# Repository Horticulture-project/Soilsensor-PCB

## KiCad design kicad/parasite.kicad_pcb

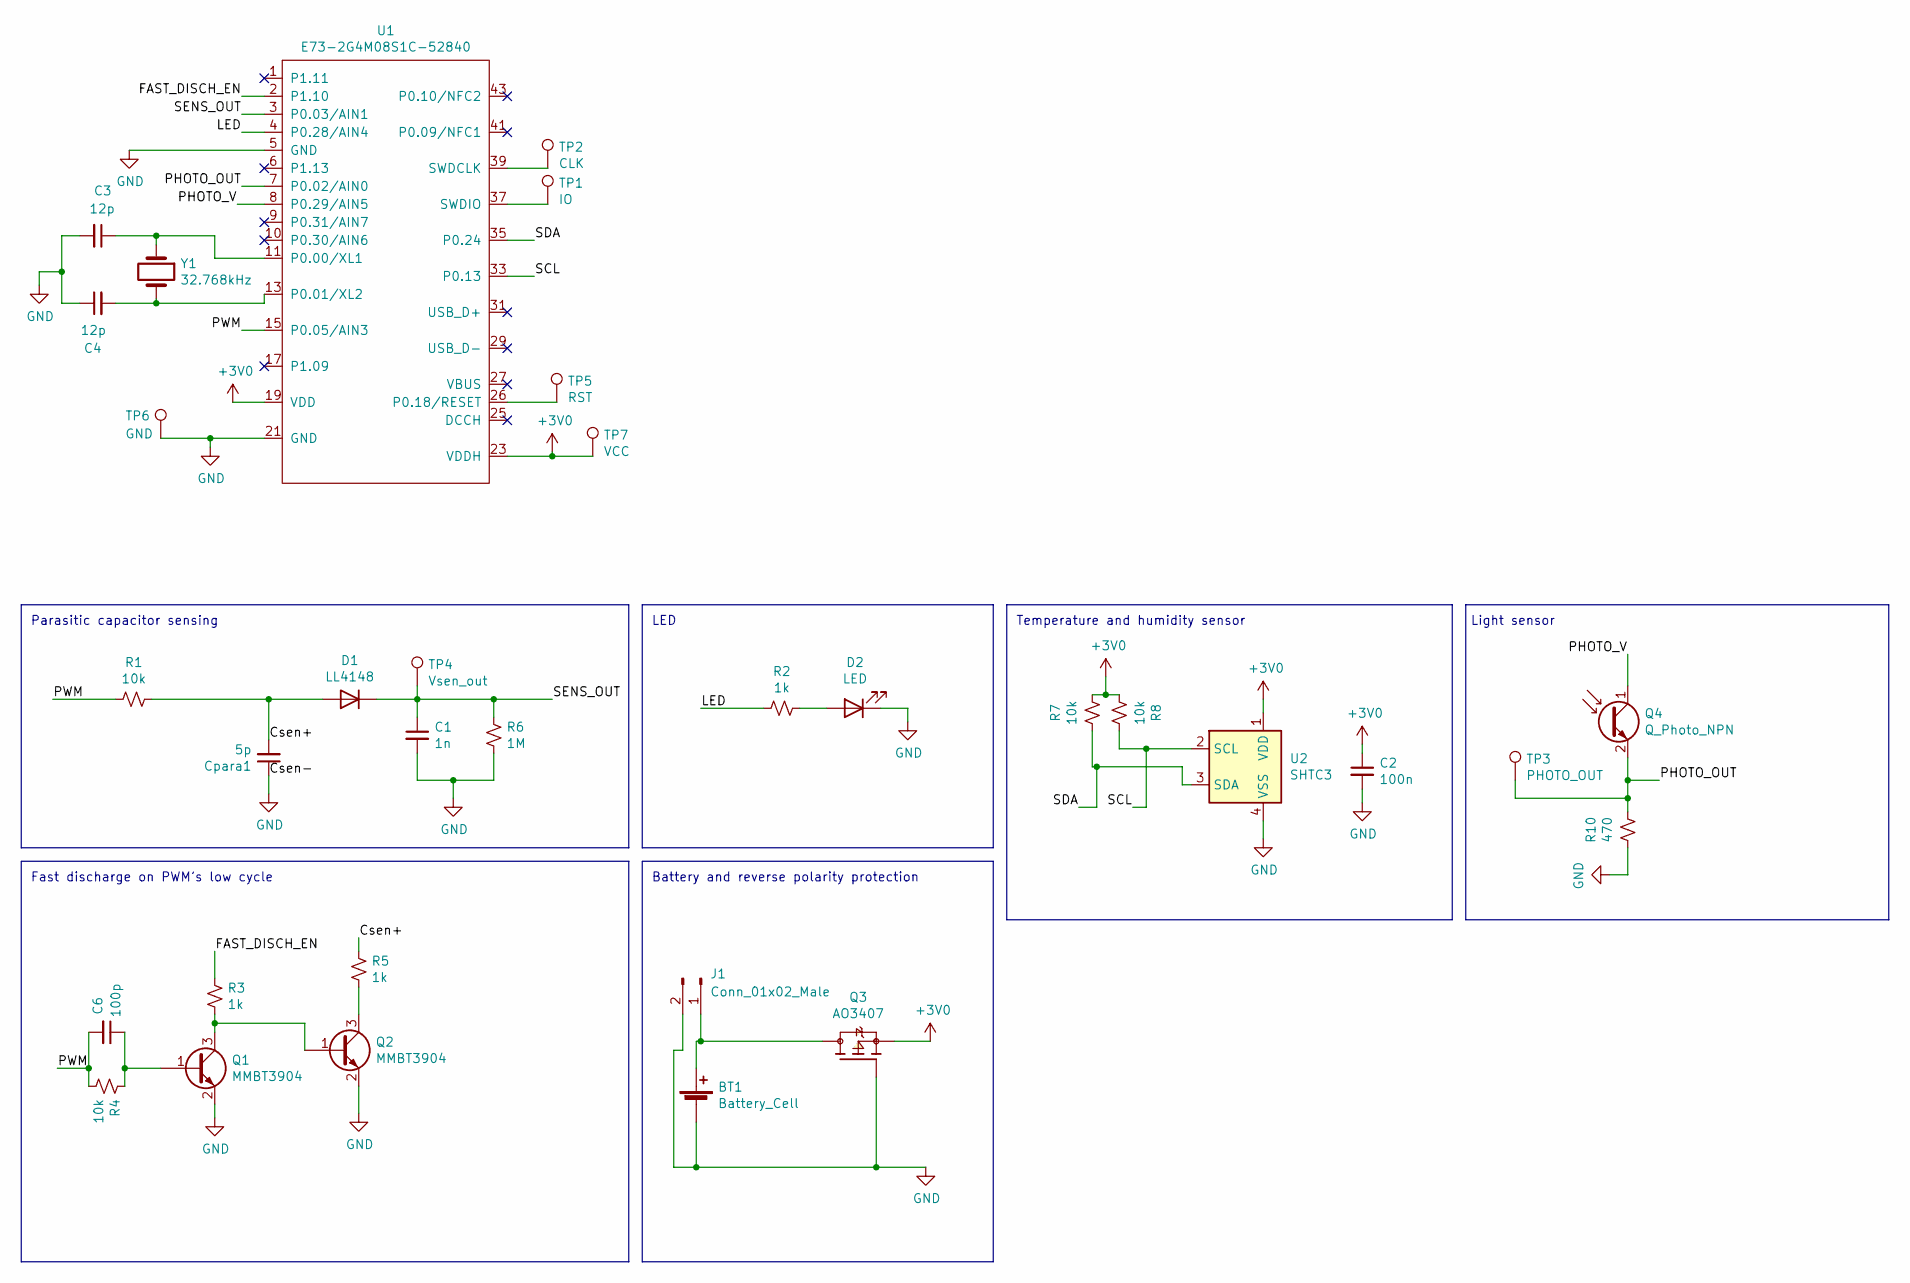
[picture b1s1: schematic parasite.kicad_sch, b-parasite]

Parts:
BT1: Battery_Cell; BatteryHolder_Keystone_3002_1x2032
C1: 1n; C_0402_1005Metric; LCSC C1523
C2: 100n; C_0402_1005Metric; LCSC C1525
C3, C4: 12p; C_0402_1005Metric; LCSC C1547
C6: 100p; C_0402_1005Metric; LCSC C1546
Cpara1: 5p; C_0805_2012Metric
D1: LL4148; D_MiniMELF; LCSC C9808
D2: LED; LED_0603_1608Metric; LCSC C2286
J1: Conn_01x02_Male; Molex_PicoBlade_53261-0271_1x02-1MP_P1.25mm_Horizontal
Q1, Q2: MMBT3904; SOT-23; LCSC C20526
Q3: AO3407; SOT-23; LCSC C181093
Q4: Q_Photo_NPN; TR8; LCSC C146233
R1, R4, R7, R8: 10k; R_0402_1005Metric; LCSC C25744
R2, R3, R5: 1k; R_0402_1005Metric; LCSC C11702
R6: 1M; R_0402_1005Metric; LCSC C26083
R10: 470; R_0402_1005Metric; LCSC C25117
TP1: IO; TestPoint_Pad_D1.0mm
TP2: CLK; TestPoint_Pad_D1.0mm
TP3: PHOTO_OUT; TestPoint_Pad_D1.0mm
TP4: Vsen_out; TestPoint_Pad_D1.0mm
TP5: RST; TestPoint_Pad_D1.0mm
TP6: GND; TestPoint_Pad_D1.0mm
TP7: VCC; TestPoint_Pad_D1.0mm
U1: E73-2G4M08S1C-52840; LCSC C356849
U2: SHTC3; Sensirion_DFN-4-1EP_2x2mm_P1mm_EP0.7x1.6mm; LCSC C194656
Y1: 32.768kHz; Crystal_SMD_3215-2Pin_3.2x1.5mm; LCSC C32346

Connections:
+3V0: C2.1, Q3.2, R7.2, R8.1, TP7.1, U1.19 (VDD), U1.23 (VDDH), U2.1 (VDD)
/Csen+: Cpara1.2, D1.2 (A), R1.2, R5.1
/FAST_DISCH_EN: R3.1, U1.2 (P1.10)
/LED: R2.1, U1.4 (P0.28/AIN4)
/PHOTO_OUT: Q4.2 (E), R10.2, TP3.1, U1.7 (P0.02/AIN0)
/PHOTO_V: Q4.1 (C), U1.8 (P0.29/AIN5)
/PWM: C6.2, R1.1, R4.2, U1.15 (P0.05/AIN3)
/SCL: R8.2, U1.33 (P0.13), U2.2 (SCL)
/SDA: R7.1, U1.35 (P0.24), U2.3 (SDA)
/SENS_OUT: C1.1, D1.1 (K), R6.1, TP4.1, U1.3 (P0.03/AIN1)
GND: BT1.2 (-), C1.2, C2.2, C3.2, C4.1, Cpara1.1, D2.1 (K), J1.2, J1.MP, Q1.2 (E), Q2.2 (E), Q3.1, R6.2, R10.1, TP6.1, U1.5 (GND), U1.21 (GND), U2.4 (VSS)
unnamed: BT1.1 (+), J1.1, Q3.3
unnamed: C3.1, U1.11 (P0.00/XL1), Y1.1
unnamed: C4.2, U1.13 (P0.01/XL2), Y1.2
unnamed: C6.1, Q1.1 (B), R4.1
unnamed: D2.2 (A), R2.2
unnamed: Q1.3 (C), Q2.1 (B), R3.2
unnamed: Q2.3 (C), R5.2
unnamed: TP1.1, U1.37 (SWDIO)
unnamed: TP2.1, U1.39 (SWDCLK)
unnamed: TP5.1, U1.26 (P0.18/RESET)

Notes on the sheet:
Light sensor
Battery and reverse polarity protection
Temperature and humidity sensor
Parasitic capacitor sensing
LED
Fast discharge on PWM’s low cycle

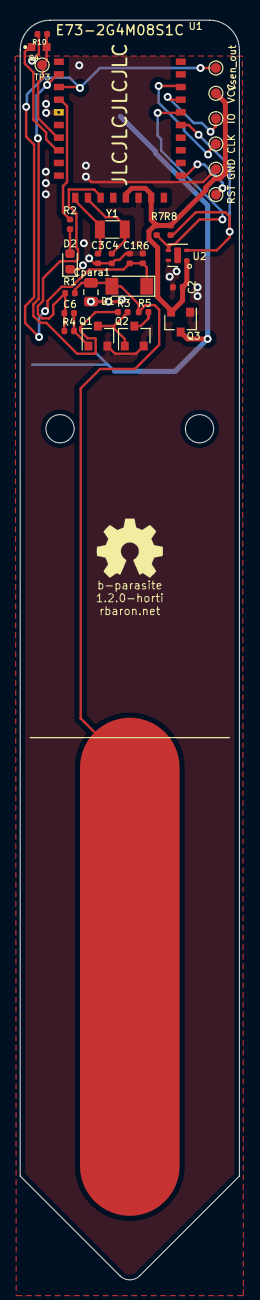
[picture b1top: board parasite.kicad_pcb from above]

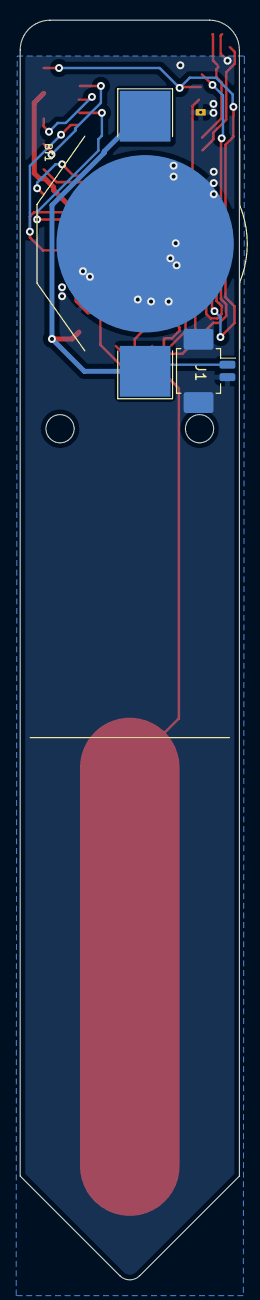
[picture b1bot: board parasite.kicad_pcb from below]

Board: 2 copper layers, 22.0 x 126.4 mm, 33 parts (2 on the bottom side), 21 nets.

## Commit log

2022-09-30 added picoblade connector
2022-11-05 Pulling new changes (#1)
    * high airflow case design stl and 3mf files
    * Added mac converter class for easy reading of mac address from microcontroller.
    * Added script for facilitating flashing procedures with pyocd.
    * Changed use of memory addresses in mac address reader to hex representation.
    * Added requirements file for python environment setup.
    * Simplified the cli of flashing scripts.
